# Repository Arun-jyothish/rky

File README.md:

# RKY 

## Multipurpose Remote Key Fob

## Functions
* Remote access ( start,horn,disable --car,bike,room)
* Display Informations, recieved from NRF24L01,WiFi
* Rolling codes
* buzzer
* vibration while near field detection
* compass directions
* preset commands in key, whenever a source device detect, it apply the commands
* disply time 

## Features

## Specifications
* Vibrator Motor
* LED BLINK
* OLED display
* WiFi connectivity
* RF transmitter
* NRF24L01
* 

~~~mermaid
graph TD
power--> ESP8266
NRF24L01--> ESP8266
OLED--> ESP8266
UART --> ESP8266
power-->NRF24L01
power-->OLED
power-->UART

~~~

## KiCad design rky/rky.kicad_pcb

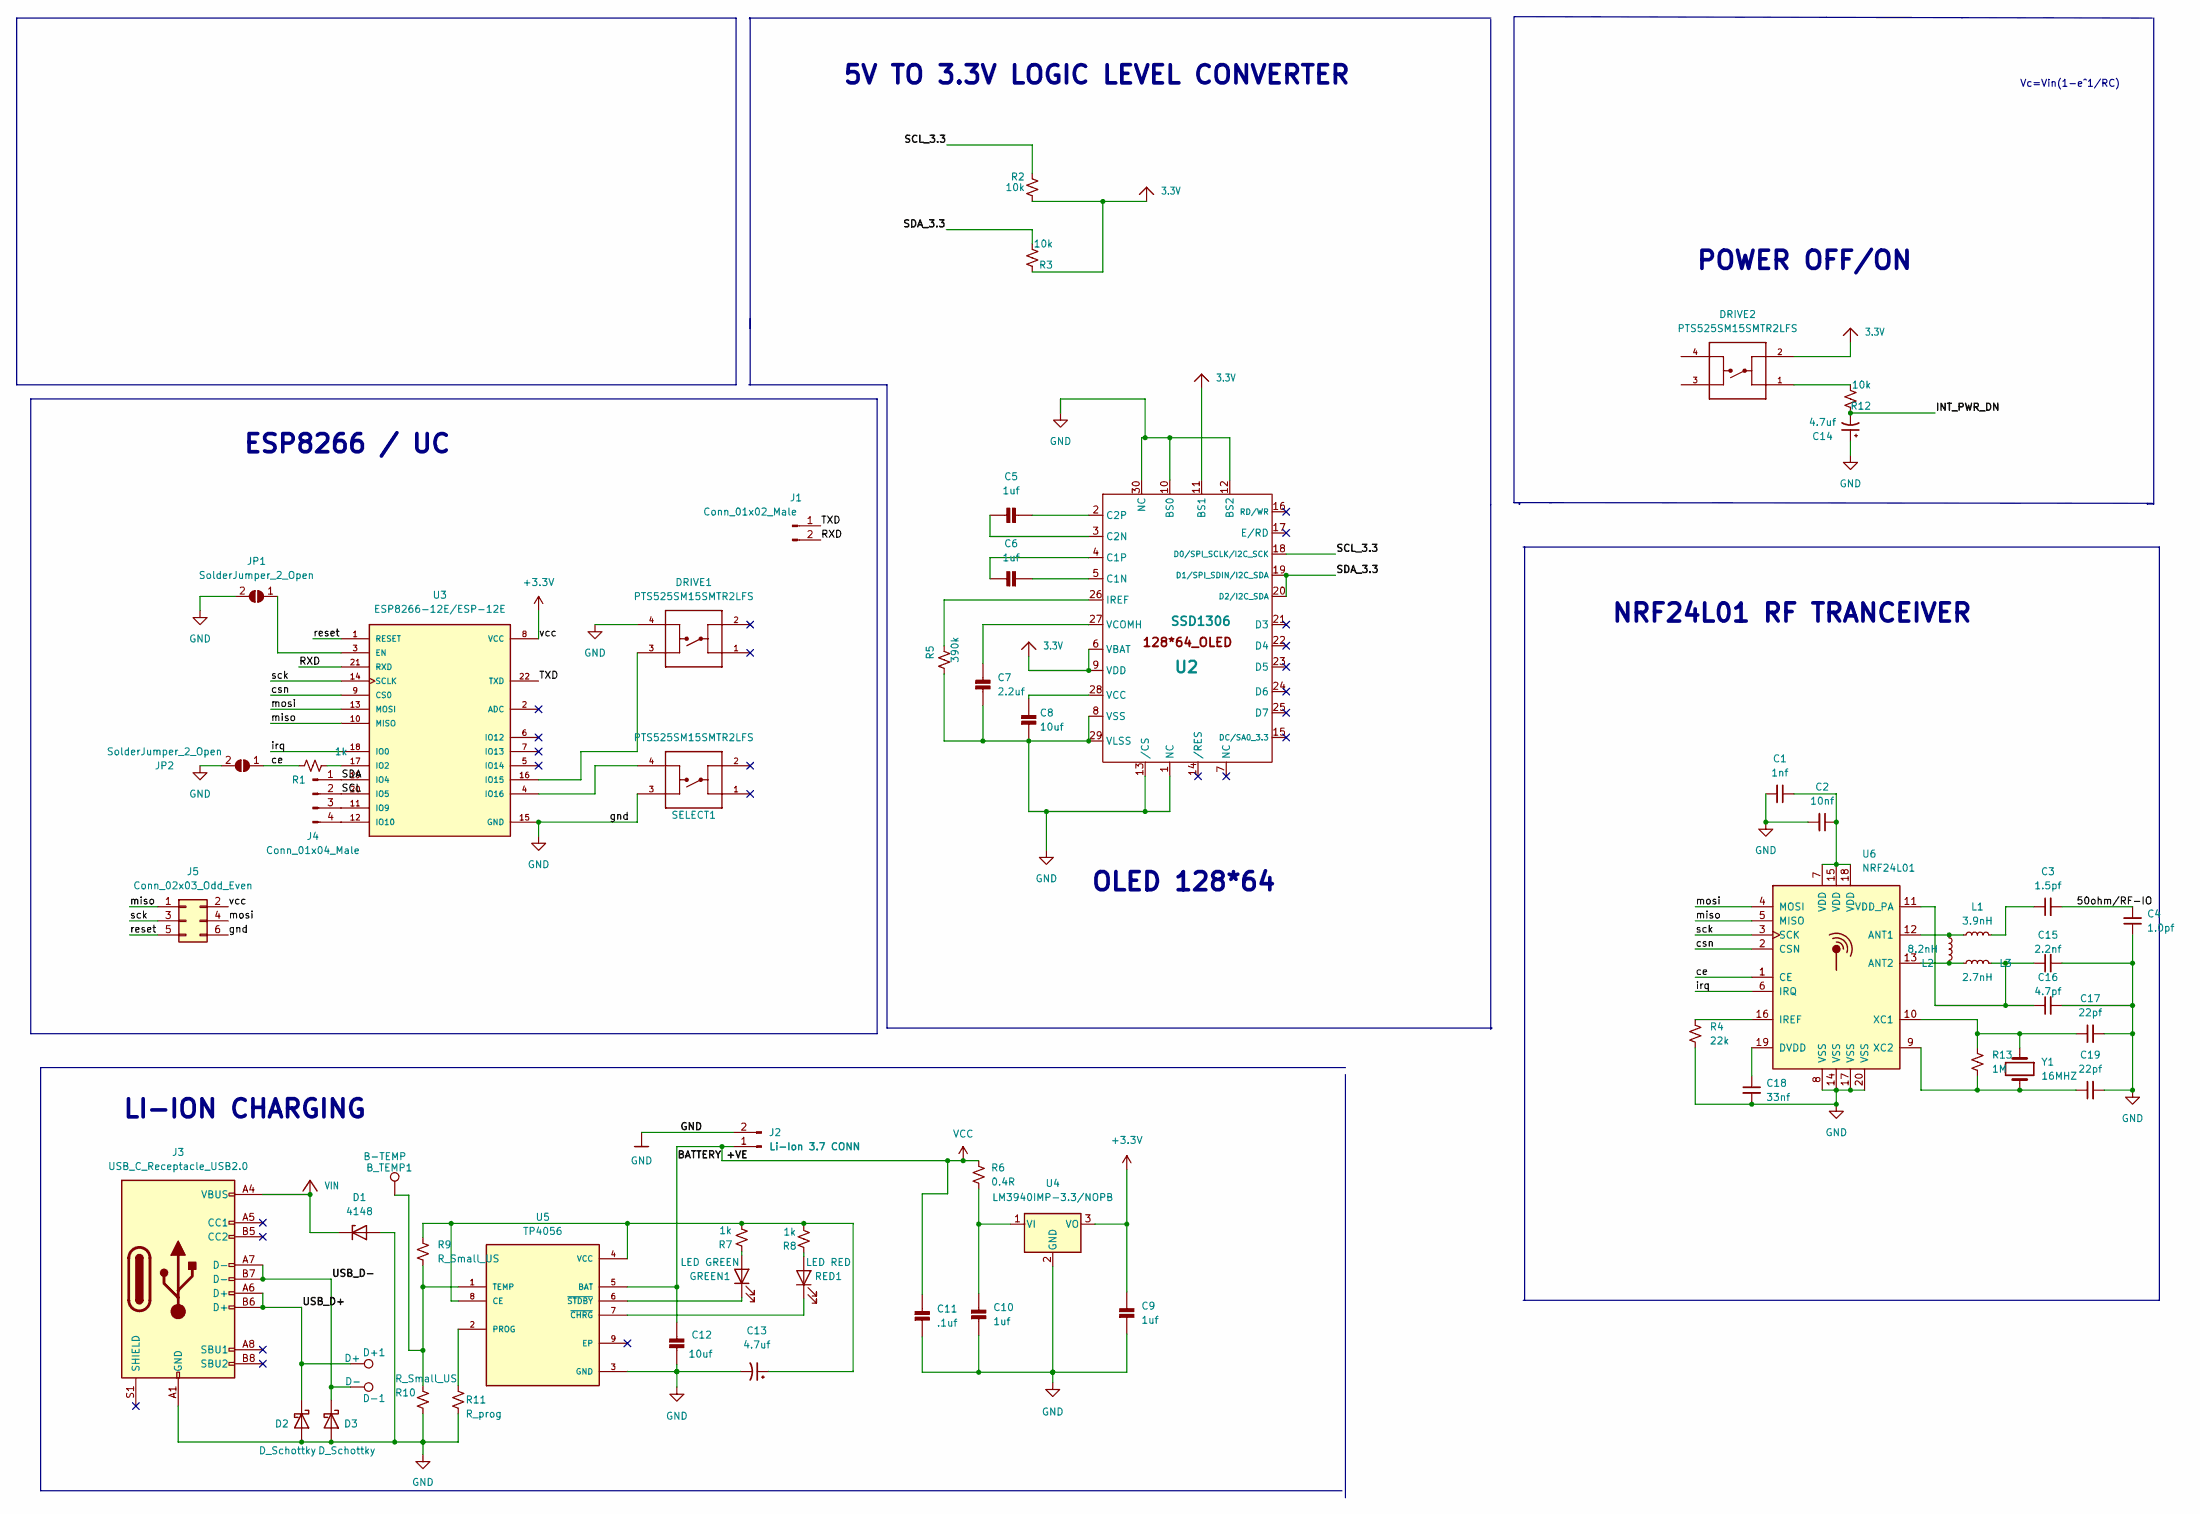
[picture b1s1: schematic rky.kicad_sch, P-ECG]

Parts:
B_TEMP1: B-TEMP; TestPoint_Pad_D1.0mm
C1: 1nf; C_0603_1608Metric_Pad1.08x0.95mm_HandSolder
C2: 10nf; C_0603_1608Metric_Pad1.08x0.95mm_HandSolder
C3: 1.5pf; C_0603_1608Metric_Pad1.08x0.95mm_HandSolder
C4: 1.0pf; C_0603_1608Metric_Pad1.08x0.95mm_HandSolder
C5, C6, C9, C10: 1uf; C_0603_1608Metric; JLC PCB PART NUMBER C2168630
C7: 2.2uf; C_0603_1608Metric; JLC PCB PART NUMBER C2858007
C8, C12: 10uf; C_0603_1608Metric; JLC PCB PART NUMBER C2167337
C11: .1uf; C_0603_1608Metric; JLC PCB PART NUMBER C2237744
C13, C14: 4.7uf; C_0603_1608Metric; JLC PCB PART NUMBER C2204347
C15: 2.2nf; C_0603_1608Metric_Pad1.08x0.95mm_HandSolder
C16: 4.7pf; C_0603_1608Metric_Pad1.08x0.95mm_HandSolder
C17, C19: 22pf; C_0603_1608Metric_Pad1.08x0.95mm_HandSolder
C18: 33nf; C_0603_1608Metric_Pad1.08x0.95mm_HandSolder
D1: 4148; D_0603_1608Metric; JLC PCB PART NUMBER C109002
D2, D3: D_Schottky; D_0603_1608Metric; JLC PCB PART NUMBER C143772
D+1: D+; TestPoint_Pad_D1.0mm
D-1: D-; TestPoint_Pad_D1.0mm
DRIVE1, DRIVE2: PTS525SM15SMTR2LFS; SW_PTS525SM15SMTR2LFS; PARTREV NA; JLC PCB PART NUMBER C221856
GREEN1: LED GREEN; LED_0603_1608Metric; JLC PCB PART NUMBER C2917809
J1: Conn_01x02_Male; PinHeader_1x02_P1.00mm_Horizontal
J2: Li-Ion 3.7 CONN; PinHeader_1x02_P1.00mm_Horizontal
J3: USB_C_Receptacle_USB2.0; USB_C_Receptacle_HRO_TYPE-C-31-M-12; JLC PCB PART NUMBER C2927026
J4: Conn_01x04_Male; PinHeader_1x04_P1.00mm_Vertical
J5: Conn_02x03_Odd_Even; PinHeader_2x03_P1.27mm_Vertical_SMD
JP1, JP2: SolderJumper_2_Open; SolderJumper-2_P1.3mm_Bridged2Bar_RoundedPad1.0x1.5mm
L1: 3.9nH
L2: 8.2nH; 8.2nG
L3: 2.7nH
R1: 1k; R_0603_1608Metric_Pad0.98x0.95mm_HandSolder
R2, R3, R12: 10k; R_0603_1608Metric; JLC PCB PART NUMBER C2930027
R4: 22k; R_0603_1608Metric_Pad0.98x0.95mm_HandSolder
R5: 390k; R_0603_1608Metric; JLC PCB PART NUMBER C304747
R6: 0.4R; R_0603_1608Metric; JLC PCB PART NUMBER C2907088
R7, R8: 1k; R_0603_1608Metric; JLC PCB PART NUMBER C2913953
R9, R10: R_Small_US; R_0603_1608Metric
R11: R_prog; R_0603_1608Metric
R13: 1M; R_0603_1608Metric_Pad0.98x0.95mm_HandSolder
RED1: LED RED; LED_0603_1608Metric; JLC PCB PART NUMBER C2917808
SELECT1: PTS525SM15SMTR2LFS; SW_PTS525SM15SMTR2LFS; PARTREV NA; JLC PCB PART NUMBER C221856
U2: SSD1306; OLED-128O064D; JLC PCB PART NUMBER C2890600
U3: ESP8266-12E/ESP-12E; XCVR_ESP8266-12E_ESP-12E
U4: LM3940IMP-3.3/NOPB; SOT-223; JLC PCB PART NUMBER C140319
U5: TP4056; SO-8_5.3x6.2mm_P1.27mm; JLC PCB PART NUMBER C725790
U6: NRF24L01; QFN-20-1EP_4x4mm_P0.5mm_EP2.5x2.5mm
Y1: 16MHZ; Crystal_SMD_0603-4Pin_6.0x3.5mm

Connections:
3.3V: DRIVE2.2, R2.1, R3.1, U2.6 (VBAT), U2.9 (VDD), U2.11 (BS1)
+3V3: C9.1, J5.2, U3.8 (VCC), U4.3 (VO)
/50ohm/RF-IO: C3.2, C4.2
/INT_PWR_DN: C14.2, R12.1
/RXD: J1.2, U3.21 (RXD)
/SCL: J4.2, U3.20 (IO5)
/SCL_3.3: R2.2, U2.18 (D0/SPI_SCLK/I2C_SCK)
/SDA: J4.1, U3.19 (IO4)
/SDA_3.3: R3.2, U2.19 (D1/SPI_SDIN/I2C_SDA), U2.20 (D2/I2C_SDA)
/TXD: J1.1, U3.22 (TXD)
/USB_D+: D2.1 (K), D+1.1, J3.A6 (D+), J3.B6 (D+)
/USB_D-: D3.1 (K), D-1.1, J3.A7 (D-), J3.B7 (D-)
/ce: JP2.1 (A), R1.1, U6.1 (CE)
/csn: U3.9 (CS0), U6.2 (CSN)
/irq: U3.18 (IO0), U6.6 (IRQ)
/miso: J5.1, U3.10 (MISO), U6.5 (MISO)
/mosi: J5.4, U3.13 (MOSI), U6.4 (MOSI)
/reset: J5.5, U3.1 (RESET)
/sck: J5.3, U3.14 (SCLK), U6.3 (SCK)
GND: C1.2, C2.2, C4.1, C7.2, C8.2, C9.2, C10.2, C11.2, C14.1, C15.2, C16.2, C17.2, C18.2, C19.2, D1.2 (A), D2.2 (A), D3.2 (A), DRIVE1.4, J2.2, J3.A1 (GND), J3.A12 (GND), J3.B1 (GND), J3.B12 (GND), J5.6, JP1.2 (B), JP2.2 (B), R4.2, R5.2, R10.1, R11.1, SELECT1.3, U2.1 (NC), U2.8 (VSS), U2.10 (BS0), U2.12 (BS2), U2.13 (/CS), U2.29 (VLSS), U2.30 (NC), U3.15 (GND), U4.2 (GND), U6.8 (VSS), U6.14 (VSS), U6.17 (VSS), U6.20 (VSS)
unnamed: B_TEMP1.1, R9.2, R10.2, U5.1 (TEMP)
unnamed: C1.1, C2.1, U6.7 (VDD), U6.15 (VDD), U6.18 (VDD)
unnamed: C3.1, L1.2
unnamed: C5.1, U2.3 (C2N)
unnamed: C5.2, U2.2 (C2P)
unnamed: C6.1, U2.4 (C1P)
unnamed: C6.2, U2.5 (C1N)
unnamed: C7.1, U2.27 (VCOMH)
unnamed: C8.1, U2.28 (VCC)
unnamed: C10.1, R6.2, U4.1 (VI)
unnamed: C12.2, C13.2, U5.3 (GND)
unnamed: C13.1, R7.2, R8.2, R9.1, U5.4 (VCC), U5.8 (CE)
unnamed: C15.1, C16.1, L3.2, U6.11 (VDD_PA)
unnamed: C17.1, R13.1, U6.10 (XC1), Y1.1
unnamed: C18.1, U6.19 (DVDD)
unnamed: C19.1, R13.2, U6.9 (XC2), Y1.2
unnamed: DRIVE1.3, U3.16 (IO15)
unnamed: DRIVE2.1, R12.2
unnamed: GREEN1.1 (K), U5.6 (~STDBY)
unnamed: GREEN1.2 (A), R7.1
unnamed: J4.3, U3.11 (IO9)
unnamed: J4.4, U3.12 (IO10)
unnamed: JP1.1 (A), U3.3 (EN)
unnamed: L1.1, L2.1, U6.12 (ANT1)
unnamed: L2.2, L3.1, U6.13 (ANT2)
unnamed: R1.2, U3.17 (IO2)
unnamed: R4.1, U6.16 (IREF)
unnamed: R5.1, U2.26 (IREF)
unnamed: R8.1, RED1.2 (A)
unnamed: R11.2, U5.2 (PROG)
unnamed: RED1.1 (K), U5.7 (~CHRG)
unnamed: SELECT1.4, U3.4 (IO16)
VCC: C11.1, C12.1, J2.1, R6.1, U5.5 (BAT)
VIN: D1.1 (K), J3.A4 (VBUS), J3.A9 (VBUS), J3.B4 (VBUS), J3.B9 (VBUS)

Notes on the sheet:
POWER OFF/ON
ESP8266 / UC
NRF24L01 RF TRANCEIVER
OLED 128*64
Vc=Vin(1-e^1/RC)
LI-ION CHARGING
5V TO 3.3V LOGIC LEVEL CONVERTER

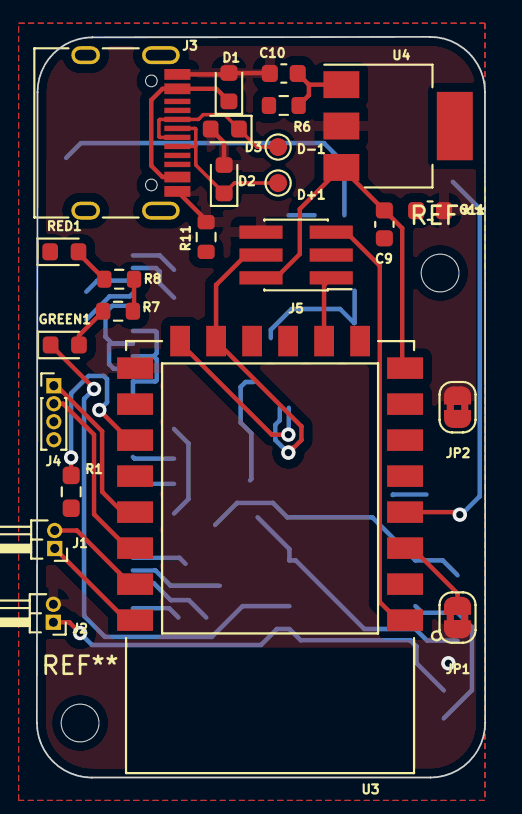
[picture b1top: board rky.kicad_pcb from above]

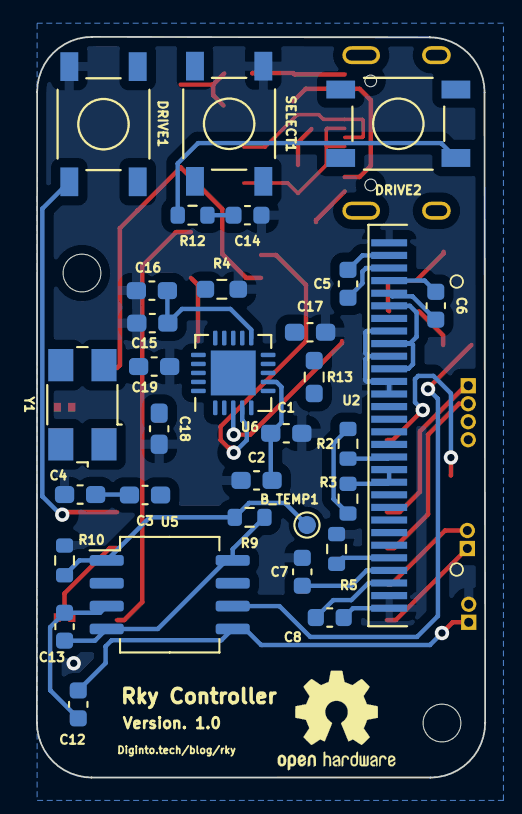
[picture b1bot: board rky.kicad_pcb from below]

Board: 2 copper layers, 24.9 x 41.1 mm, 56 parts (32 on the bottom side), 51 nets.

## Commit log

2022-06-10 rough pcb layout create
2022-06-11 schematic update
2022-07-02 remove cp2102
    new layout
2022-07-03 component place
    first touch component placement complete
2022-07-09 add render folder
    kicad 3d render image folder add
2022-07-18 update README
    add render images
2022-07-18 patch1
2022-07-18 patch2
